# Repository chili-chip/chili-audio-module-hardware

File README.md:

# chili-audio-module

KiCad 10 project for the **chilichip audio module**: a tiny I²S mono speaker amplifier based on the [MAX98357A](https://www.analog.com/media/en/technical-documentation/data-sheets/MAX98357A-MAX98357B.pdf), made to be soldered flat onto a host board through castellated edge pads. It is the audio board for [chilichip](https://chilichip.eu)'s [VGC Zero](https://github.com/chili-chip/vgc-zero-hardware) game console, and works with any 3.3 V microcontroller that can output I²S (RP2040/RP2350, ESP32, …).

Current revision: **v1.1.1**

| Top | Bottom |
|:---:|:---:|
|  |  |

## Specifications

| | |
|---|---|
| Amplifier | MAX98357A: I²S in, filterless class D out, no MCLK needed |
| Gain | 12 dB (GAIN_SLOT tied to GND) |
| Channel | Mono (L+R)/2 mix when MODE is driven at 3.3 V |
| Supply | 3.3 V |
| Speaker output | Molex PicoBlade 1.25 mm 2-pin connector (J3), for a 4–8 Ω speaker |
| Board | 11.5 × 17.5 mm, 2 layers, 1.6 mm, all parts on the top side |
| Host connection | 6 castellated half-holes, 2.54 mm pitch |

The speaker output is bridge-tied (OUTP/OUTN). Connect the speaker across the two connector pins, and don't tie either one to ground.

## Pinout

Seen from the top, with the speaker connector at the top edge. Positions are pad centres, measured from the board's bottom-left corner.

| Pad | Signal | Edge | Position | Description |
|-----|--------|------|----------|-------------|
| J1.4 | MODE | left | y = 10.12 mm | Enable. High (3.3 V) = on, mono mix. Low = shutdown. Goes to SD_MODE through R1 (510 kΩ) |
| J1.3 | LRCLK | left | y = 7.58 mm | I²S word select (labelled LCLK on the silkscreen) |
| J1.2 | BCLK | left | y = 5.04 mm | I²S bit clock |
| J1.1 | DIN | left | y = 2.50 mm | I²S data |
| J2.2 | GND | bottom | x = 6.46 mm | Ground |
| J2.1 | 3V3 | bottom | x = 9.00 mm | 3.3 V supply |

The amplifier accepts standard I²S, left-justified and TDM audio. Drive MODE from a GPIO to switch the amplifier off when idle, or tie it to 3V3 to keep it always on.

## Bill of materials

| Ref | Part | Package | LCSC |
|-----|------|---------|------|
| U1 | MAX98357AETE+T | TQFN-16 3 × 3 mm | [C910544](https://www.lcsc.com/product-detail/C910544.html) |
| J3 | Molex 53261-0271, PicoBlade 2-pin, right angle | SMD | [C177225](https://www.lcsc.com/product-detail/C177225.html) |
| C1 | 10 µF, 6.3 V, X5R | 0402 | [C15525](https://www.lcsc.com/product-detail/C15525.html) |
| C2 | 100 nF, 16 V, X7R | 0402 | [C1525](https://www.lcsc.com/product-detail/C1525.html) |
| R1 | 510 kΩ, 1 % | 0603 | [C23192](https://www.lcsc.com/product-detail/C23192.html) |

J1 and J2 are the castellated edge pads, which are part of the board itself, so there's nothing to buy or place for them.

## Ordering from JLCPCB

Every tagged release has the files JLCPCB needs attached, for both bare PCBs and assembled boards:

- `chili-audio-module-<version>-gerbers.zip`: Gerbers and drill file
- `chili-audio-module-<version>-bom.csv`: bill of materials with LCSC part numbers
- `chili-audio-module-<version>-cpl.csv`: component placement list

1. Download the three files from the [latest release](https://github.com/chili-chip/chili-audio-module-hardware/releases/latest).
2. On [jlcpcb.com](https://jlcpcb.com/), click **Order now** and upload the gerber zip.
3. Set the PCB options:
   - Layers: **2**
   - PCB thickness: **1.6 mm**
   - **Castellated Holes: Yes** (required, because the module's pads are plated half-holes)
   - Surface finish: **ENIG** recommended, for the flat QFN pads and castellations. HASL also works.
   - Everything else can stay at the defaults.
4. For assembled boards, turn on **PCB Assembly**, choose **Top side** assembly, and click **Next**. If the Economic assembly option isn't available together with castellated holes, choose Standard.
5. Upload the BOM and CPL files and check that all five parts (C1, C2, J3, R1, U1) are matched and in stock. The MAX98357A and the connector are usually "extended" parts, which add a small one-off fee each.
6. In the part placement preview, check that:
   - **U1**'s pin 1 dot is in the bottom-left corner, next to the triangle on the silkscreen. Rotate it in the preview if not.
   - **J3**'s opening faces the top edge of the board, with its two mounting tabs on the large pads.
7. Add to cart and place the order.

To build the files from a local checkout instead, run `scripts/export-jlcpcb.sh` (needs KiCad 10's `kicad-cli`, `zip` and `python3`). The files are written to `production/`.

## Using the module on a host board

- On the host board, place SMD pads matching the castellations: four along one edge at 2.54 mm pitch, and two along the adjacent edge. The positions are in the [pinout](#pinout) table.
- `chili-audio-module-hardware.step` is a 3D model of the assembled module, with its origin at the bottom-left corner of the board. Assign it to the host board's footprint with no offset, so the module sits flat on the host.
- Keep the host board free of tall parts under the module.

## Repository layout

| Path | Contents |
|------|----------|
| `chili-audio-module-hardware.kicad_*` | KiCad 10 schematic, PCB and project |
| `chili-audio-module.pretty/` | Project footprints (castellated edge pads) |
| `chili-audio-module-hardware.step` | 3D model of the assembled module |
| `scripts/export-jlcpcb.sh` | Builds the JLCPCB Gerber zip, BOM and CPL |
| `scripts/render-images.sh` | Regenerates the renders in `docs/images/` |
| `.github/workflows/main.yml` | CI and release workflow |

CI runs ERC, DRC and the JLCPCB export on every push and pull request. Pushing a `v*` tag publishes a GitHub release with the schematic PDF, a PCB image, Gerbers and the JLCPCB files.

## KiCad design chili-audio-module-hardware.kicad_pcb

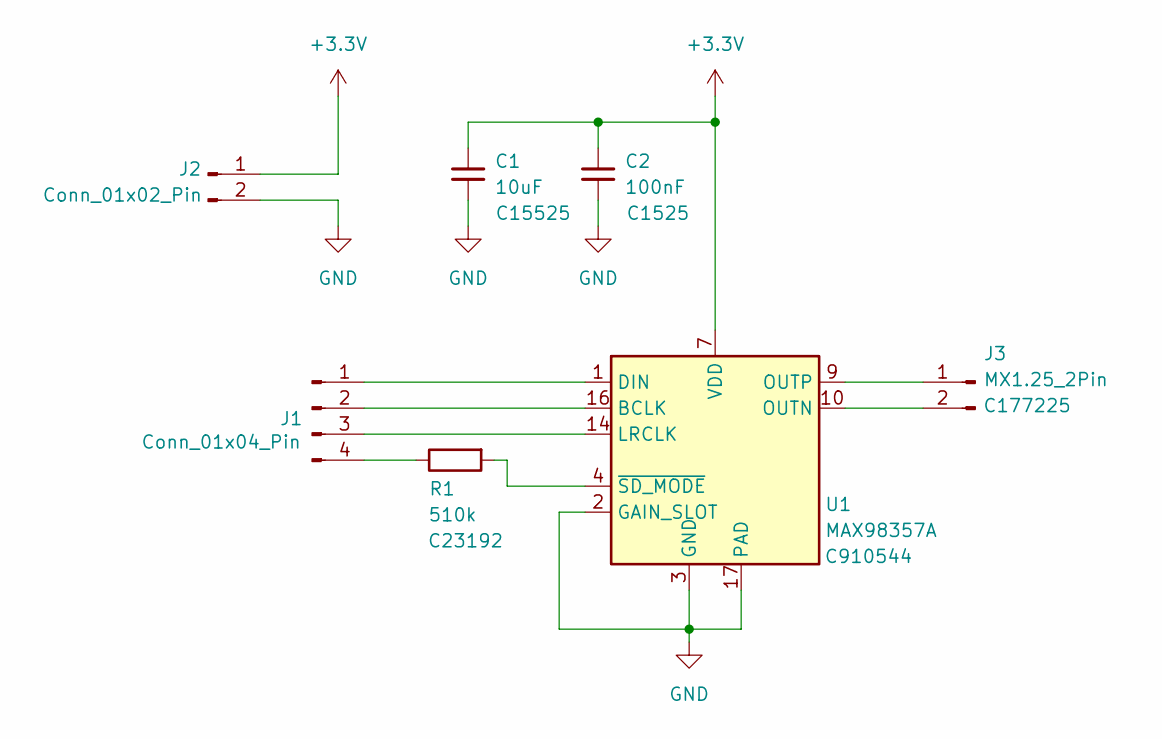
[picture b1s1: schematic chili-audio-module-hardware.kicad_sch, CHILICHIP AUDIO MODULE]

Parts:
C1: 10uF; C_0402_1005Metric; LCSC C15525
C2: 100nF; C_0402_1005Metric; LCSC C1525
J1: Conn_01x04_Pin; Castellated_1x04_P2.54mm
J2: Conn_01x02_Pin; Castellated_1x02_P2.54mm
J3: MX1.25_2Pin; Molex_PicoBlade_53261-0271_1x02-1MP_P1.25mm_Horizontal; LCSC C177225
R1: 510k; R_0603_1608Metric; LCSC C23192
U1: MAX98357A; TQFN-16-1EP_3x3mm_P0.5mm_EP1.23x1.23mm_ThermalVias; LCSC C910544

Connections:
+3.3V: C1.1, C2.1, J2.1, U1.7 (VDD), U1.8 (VDD)
GND: C1.2, C2.2, J2.2, U1.2 (GAIN_SLOT), U1.3 (GND), U1.11 (GND), U1.15 (GND), U1.17 (PAD)
unnamed: J1.1, U1.1 (DIN)
unnamed: J1.2, U1.16 (BCLK)
unnamed: J1.3, U1.14 (LRCLK)
unnamed: J1.4, R1.1
unnamed: J3.1, U1.9 (OUTP)
unnamed: J3.2, U1.10 (OUTN)
unnamed: R1.2, U1.4 (~SD_MODE)

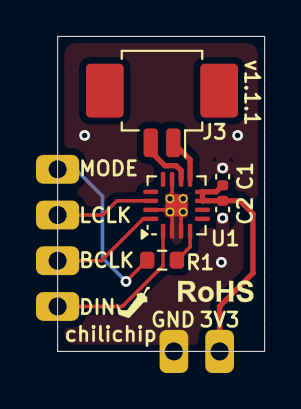
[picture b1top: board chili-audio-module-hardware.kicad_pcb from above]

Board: 2 copper layers, 11.5 x 17.5 mm, 8 parts (0 on the bottom side), 9 nets.

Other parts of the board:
ROHS: RoHS-Logo_6mm_SilkScreen
